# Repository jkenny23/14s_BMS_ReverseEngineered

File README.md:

# 14s_BMS_ReverseEngineered
Reverse Engineered Schematic/Layout of a "standard" 14s Dumb BMS

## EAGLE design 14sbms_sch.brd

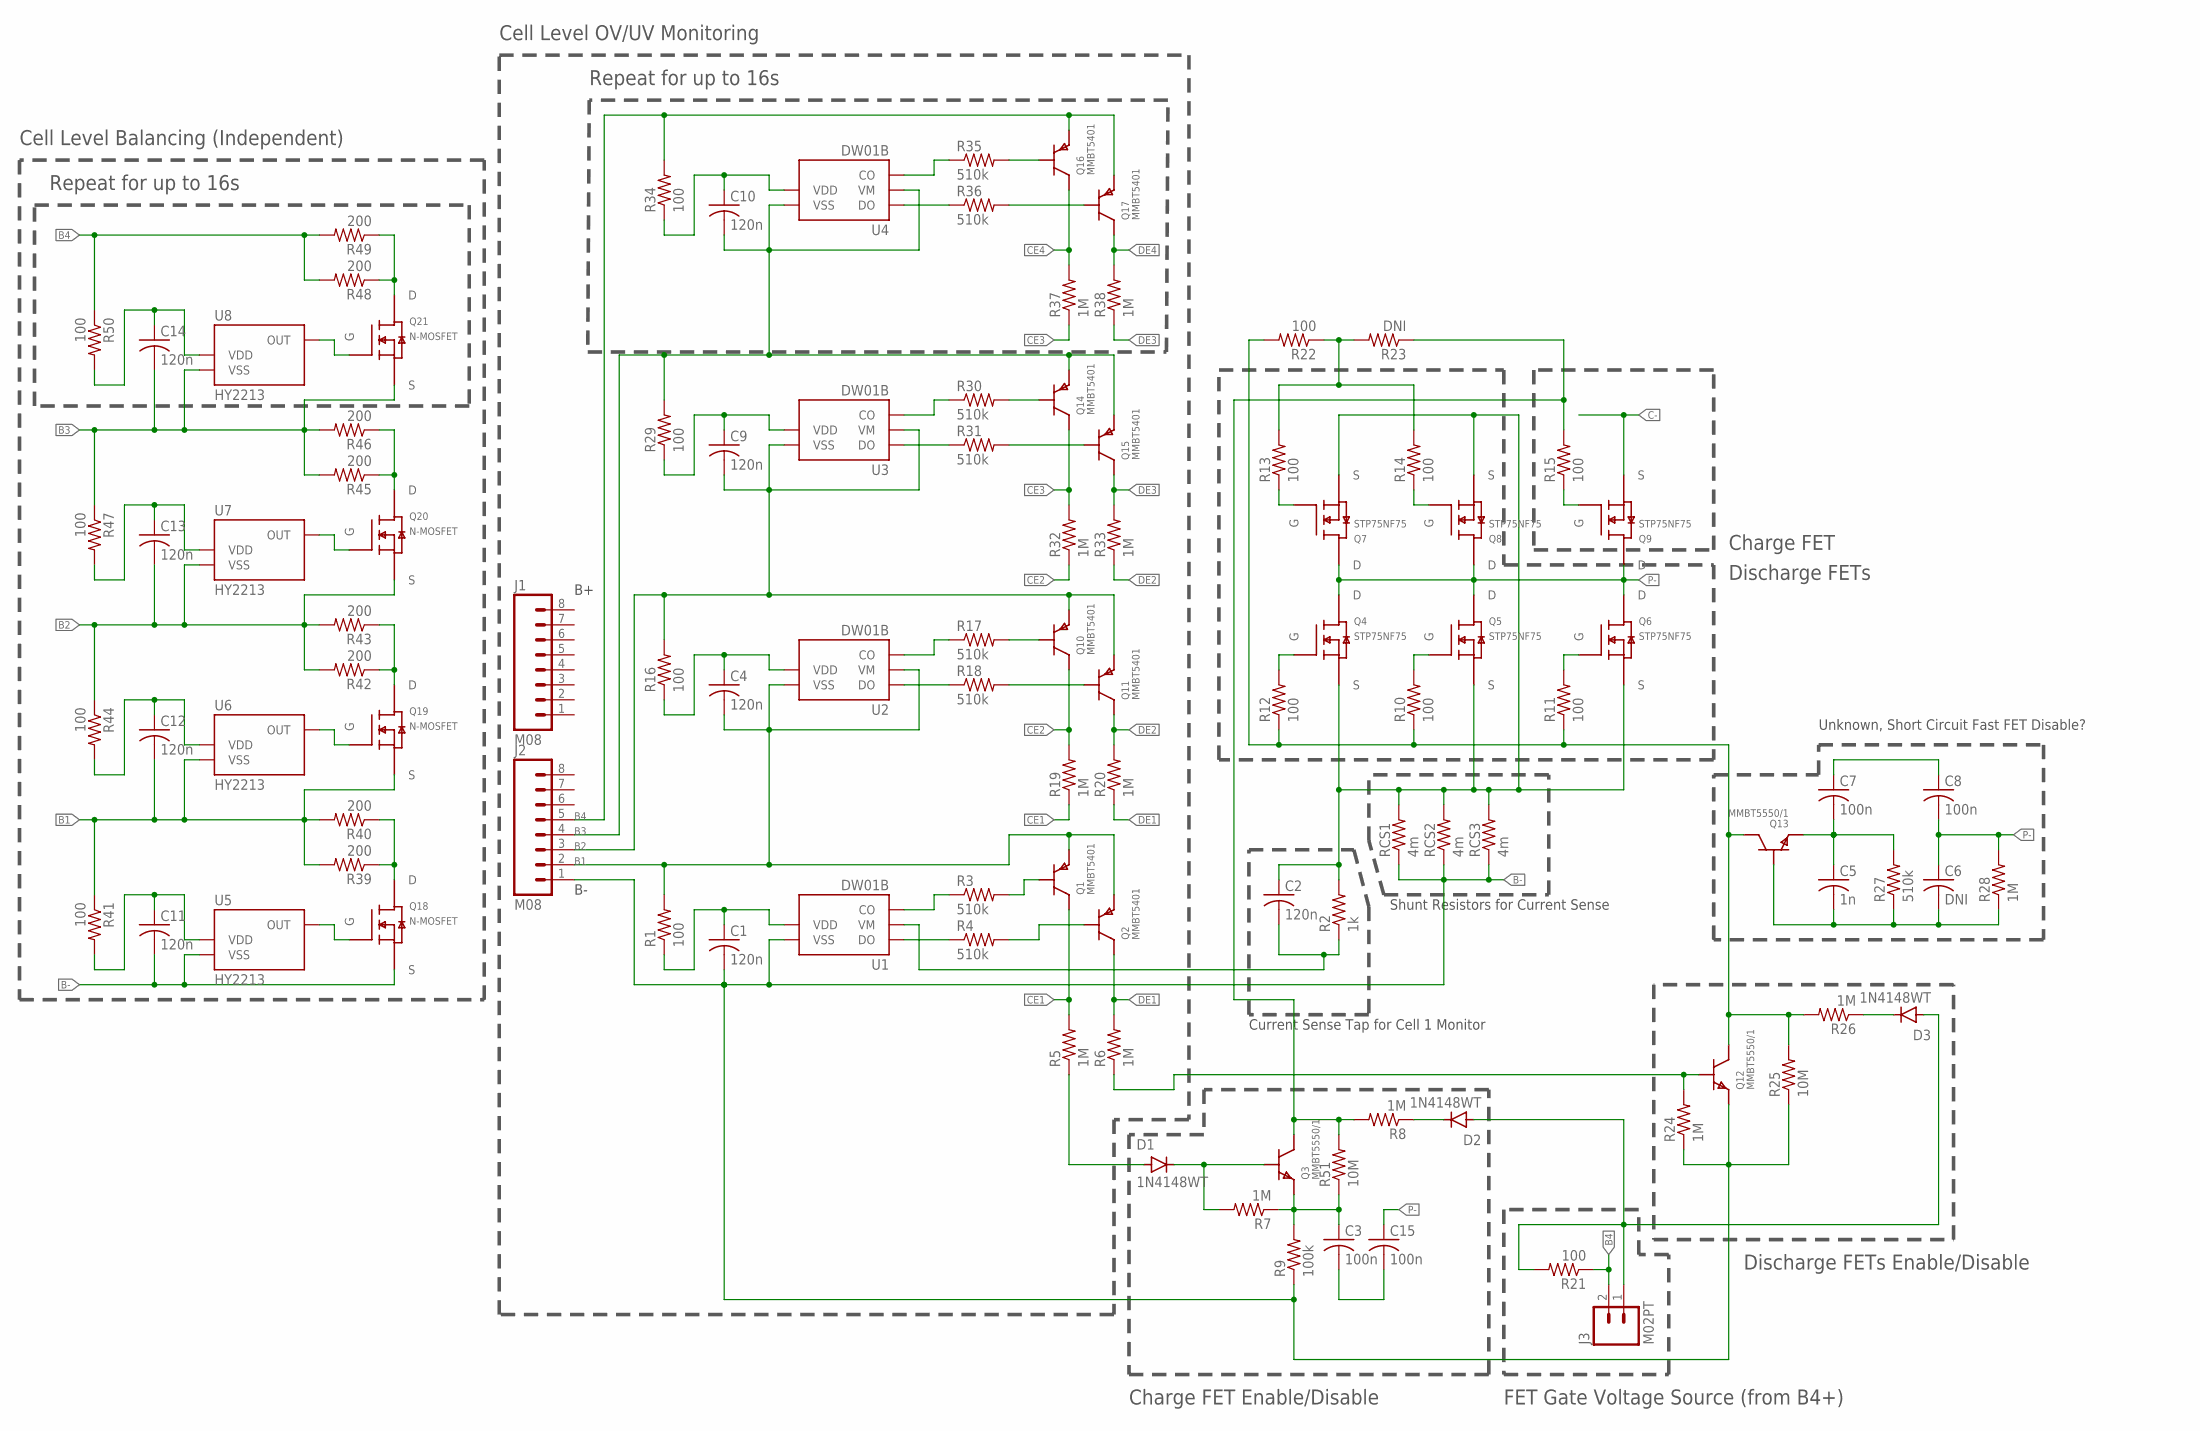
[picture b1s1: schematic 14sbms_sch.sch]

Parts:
C1, C2, C4, C9, C10, C11, C12, C13, C14: 120n; C0603
C3, C15: 100n; C0603
C5: 1n; C0603
C6: DNI; C0603
C7, C8: 100n; C0805
D1, D2, D3: 1N4148WT; SOD523
J1, J2: M08; S8B-XH-A
J3: M02PT; PHOENIXCONTACT1935161
Q1, Q2, Q10, Q11, Q14, Q15, Q16, Q17: MMBT5401; SOT23
Q3, Q12, Q13: MMBT5550/1; SOT23
Q4, Q5, Q6, Q7, Q8, Q9: STP75NF75; D2PAK-ST
Q18, Q19, Q20, Q21: N-MOSFET; SOT23
R1, R10, R11, R12, R13, R14, R15, R16, R21, R22, R29, R34, R41, R44, R47, R50: 100; R0603
R2: 1k; R0603
R3, R4, R17, R18, R27, R30, R31, R35, R36: 510k; R0603
R5, R6, R7, R8, R19, R20, R24, R26, R28, R32, R33, R37, R38: 1M; R0603
R9: 100k; R0603
R23: DNI; R0603
R25, R51: 10M; R0603
R39, R40, R42, R43, R45, R46, R48, R49: 200; R1206
RCS1, RCS2, RCS3: 4m; R2512
U1, U2, U3, U4: DW01B; SOT23-6
U5, U6, U7, U8: HY2213; SOT23-6

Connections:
B1: C4.2, C12.2, J2.2, Q1.2 (E), Q2.2 (E), Q19.2 (S), R1.2, R39.2, R40.2, R41.1, U2.2 (VM), U2.6 (VSS), U6.3 (VSS)
B2: C9.2, C13.2, J2.3, Q10.2 (E), Q11.2 (E), Q20.2 (S), R16.2, R42.2, R43.2, R44.1, U3.2 (VM), U3.6 (VSS), U7.3 (VSS)
B3: C10.2, C14.2, J2.4, Q14.2 (E), Q15.2 (E), Q21.2 (S), R29.2, R45.2, R46.2, R47.1, U4.2 (VM), U4.6 (VSS), U8.3 (VSS)
B4: J2.5, J3.2, Q16.2 (E), Q17.2 (E), R21.1, R34.2, R48.2, R49.2, R50.1
B-: C1.2, C11.2, J2.1, Q12.2 (E), Q18.2 (S), R9.1, R24.1, R25.1, RCS1.1, RCS2.1, RCS3.1, U1.6 (VSS), U5.3 (VSS)
BALG1: Q18.1 (G), U5.6 (OUT)
BALG2: Q19.1 (G), U6.6 (OUT)
BALG3: Q20.1 (G), U7.6 (OUT)
BALG4: Q21.1 (G), U8.6 (OUT)
C-: Q9.3-S (S)
CE1: Q1.3 (C), R5.2, R19.1
CE2: Q10.3 (C), R19.2, R32.1
CE3: Q14.3 (C), R32.2, R37.1
CE4: Q16.3 (C), R37.2
DE1: Q2.3 (C), R6.2, R20.1
DE2: Q11.3 (C), R20.2, R33.1
DE3: Q15.3 (C), R33.2, R38.1
DE4: Q17.3 (C), R38.2
GS+: D2.A (ANODE), D3.A (ANODE), J3.1, R21.2
unnamed: R4.1, U1.1 (DO)
unnamed: C1.1, R1.1, U1.5 (VDD)
unnamed: Q3.3 (C), R8.2, R15.2, R23.1, R51.2
unnamed: C2.2, R2.1, U1.2 (VM)
unnamed: Q7.1-G (G), R13.1
unnamed: R3.1, U1.3 (CO)
unnamed: Q1.1 (B), R3.2
unnamed: Q2.1 (B), R4.2
unnamed: C3.1, Q3.2 (E), R7.1, R9.2, R51.1
unnamed: D1.A (ANODE), R5.1
unnamed: D1.K (CATHODE), Q3.1 (B), R7.2
unnamed: D2.K (CATHODE), R8.1
unnamed: Q8.1-G (G), R14.1
unnamed: Q9.1-G (G), R15.1
unnamed: Q6.1-G (G), R11.2
unnamed: Q5.1-G (G), R10.2
unnamed: Q4.1-G (G), R12.2
unnamed: R13.2, R14.2, R22.1, R23.2
unnamed: Q12.3 (C), Q13.3 (C), R10.1, R11.1, R12.1, R22.2, R25.2, R26.2
unnamed: Q17.1 (B), R36.2
unnamed: Q16.1 (B), R35.2
unnamed: Q11.1 (B), R18.2
unnamed: Q10.1 (B), R17.2
unnamed: R17.1, U2.3 (CO)
unnamed: R18.1, U2.1 (DO)
unnamed: C7.1, C8.1
unnamed: Q12.1 (B), R6.1, R24.2
unnamed: C4.1, R16.1, U2.5 (VDD)
unnamed: C5.1, C7.2, Q13.2 (E), R27.2
unnamed: R35.1, U4.3 (CO)
unnamed: D3.K (CATHODE), R26.1
unnamed: C5.2, C6.2, Q13.1 (B), R27.1, R28.1
unnamed: R36.1, U4.1 (DO)
unnamed: Q15.1 (B), R31.2
unnamed: Q14.1 (B), R30.2
unnamed: R30.1, U3.3 (CO)
unnamed: R31.1, U3.1 (DO)
unnamed: C9.1, R29.1, U3.5 (VDD)
unnamed: C10.1, R34.1, U4.5 (VDD)
unnamed: C11.1, R41.2, U5.2 (VDD)
unnamed: Q18.3 (D), R39.1, R40.1
unnamed: C12.1, R44.2, U6.2 (VDD)
unnamed: Q19.3 (D), R42.1, R43.1
unnamed: C13.1, R47.2, U7.2 (VDD)
unnamed: Q20.3 (D), R45.1, R46.1
unnamed: C14.1, R50.2, U8.2 (VDD)
unnamed: Q21.3 (D), R48.1, R49.1
unnamed: C3.2, C15.2
P-: C6.1, C8.2, C15.1, Q4.2-D (D), Q5.2-D (D), Q6.2-D (D), Q7.2-D (D), Q8.2-D (D), Q9.2-D (D), R28.2
S: C2.1, Q4.3-S (S), Q5.3-S (S), Q6.3-S (S), Q7.3-S (S), Q8.3-S (S), R2.2, RCS1.2, RCS2.2, RCS3.2

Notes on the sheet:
Repeat for up to 16s
Cell Level OV/UV Monitoring
Charge FET Enable/Disable
Discharge FETs Enable/Disable
FET Gate Voltage Source (from B4+)
Shunt Resistors for Current Sense
Current Sense Tap for Cell 1 Monitor
Discharge FETs
Charge FET
Cell Level Balancing (Independent)
Unknown, Short Circuit Fast FET Disable?

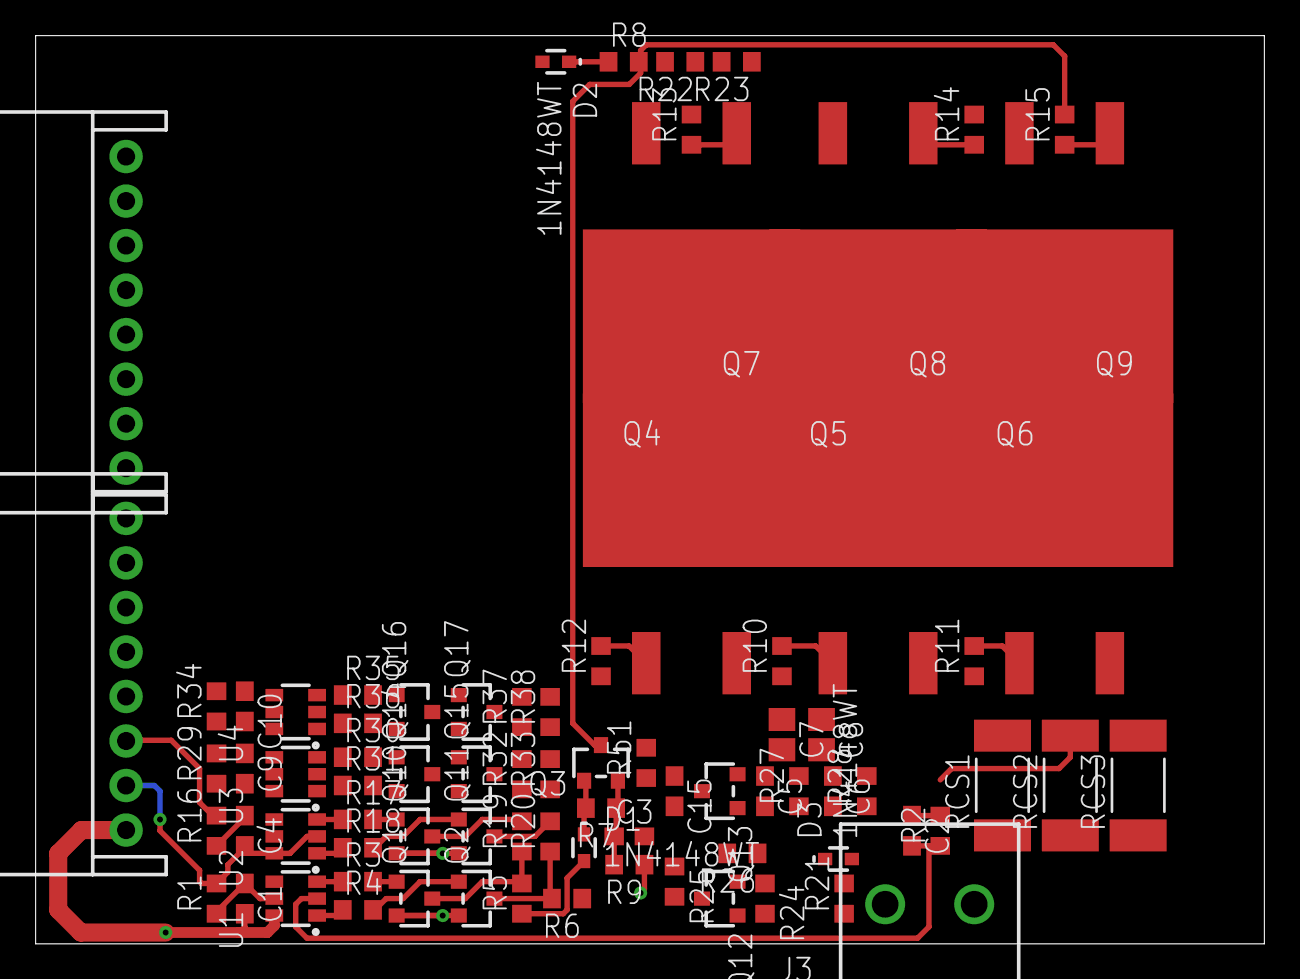
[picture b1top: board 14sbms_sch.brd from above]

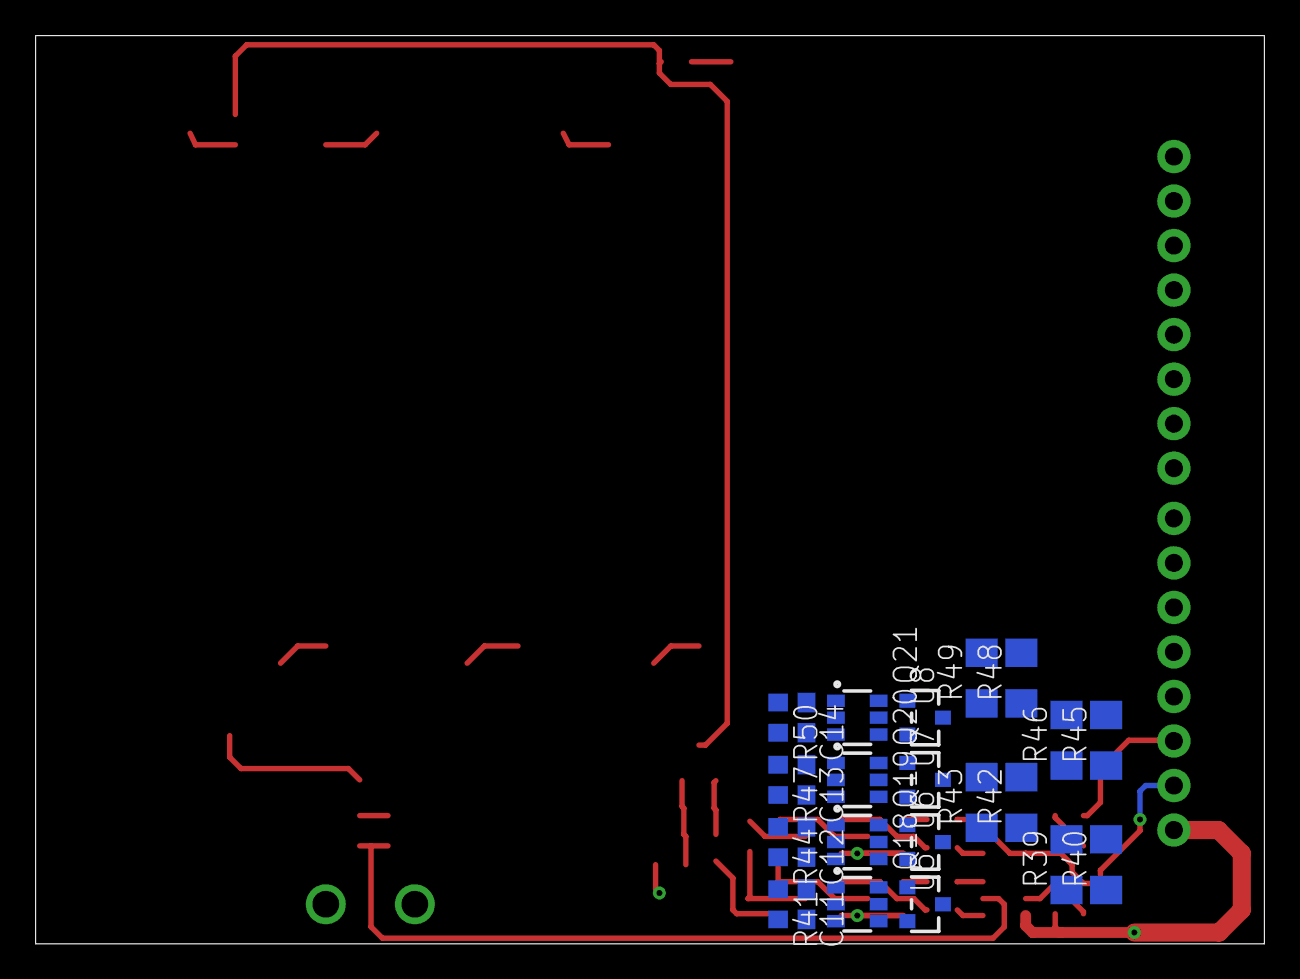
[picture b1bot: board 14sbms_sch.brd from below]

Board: 2 copper layers, 69.0 x 51.0 mm, 104 parts (24 on the bottom side), 68 nets.
